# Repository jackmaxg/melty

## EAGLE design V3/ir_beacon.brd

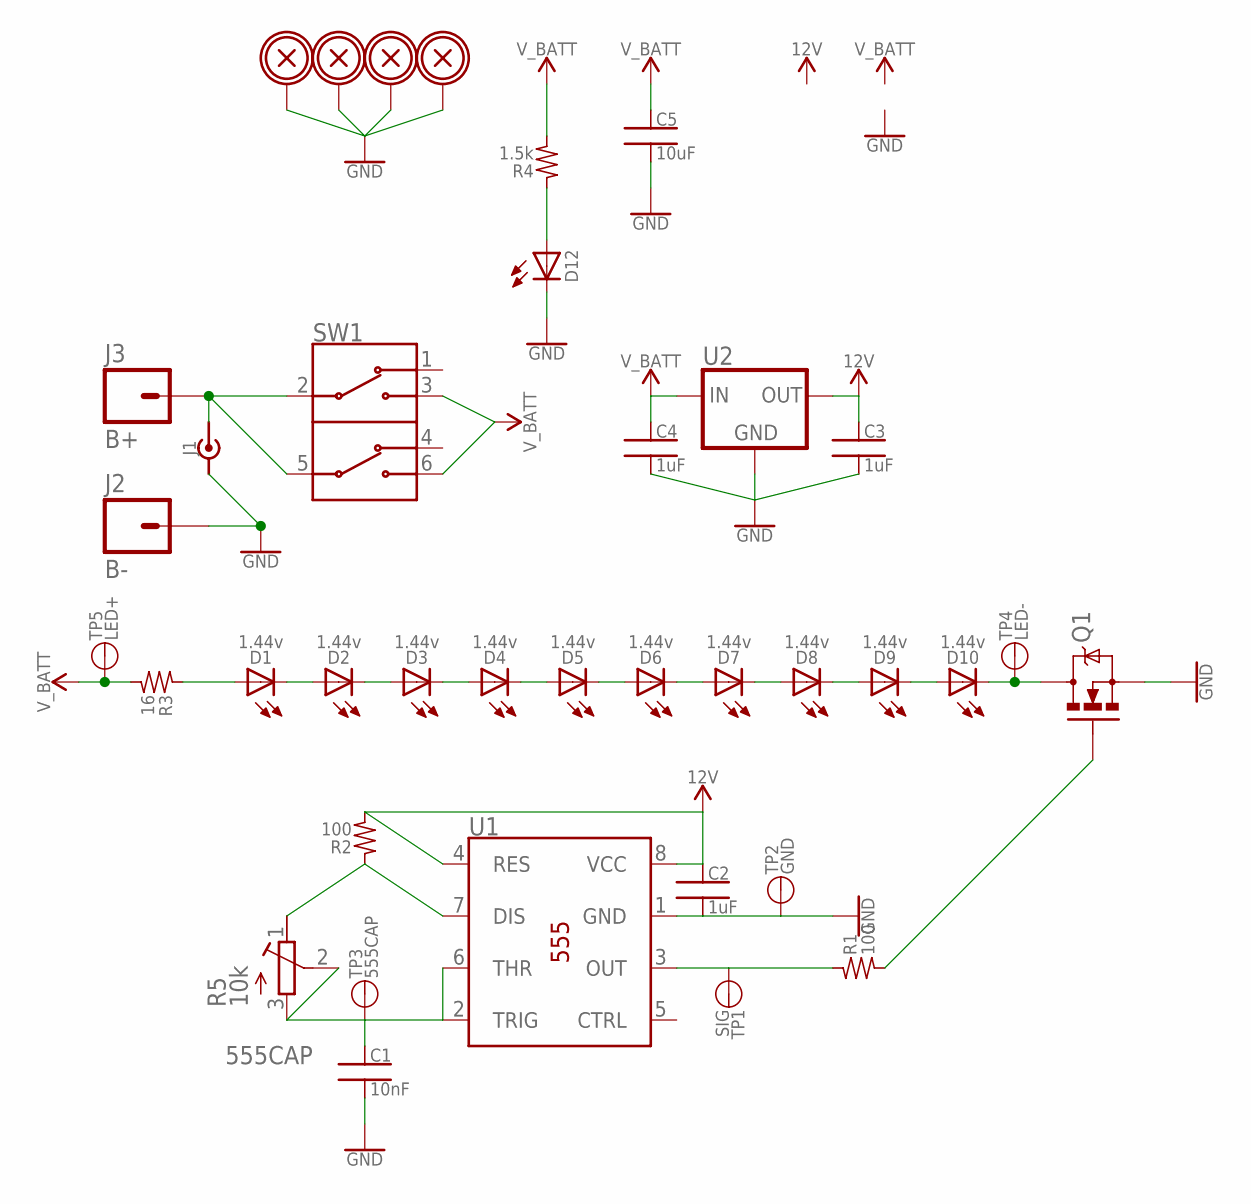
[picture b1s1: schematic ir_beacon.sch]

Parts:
C1: 10nF; CAP-PTH-.1"
C2, C3, C4: 1uF; 0805
C5: 10uF; 0805
D1, D2, D3, D4, D5, D6, D7, D8, D9, D10: 1.44v; PLCC-2
D12: LED1206; LED-1206
H1, H2, H3, H4: BOLTHOLE_M3; M3_HOLE
J1: PJ-082BH
J2: B-; 14AWG_PTH
J3: B+; 14AWG_PTH
Q1: MOSFET_N-CHANNEL_DPAK; DPAK
R1, R2: 100; 0805
R3: 16; 1206
R4: 1.5k; 0805
R5: 10k; 3296W
SW1: CNK-L202_MS02; CNK-L202XXXMS02XXX
TP1: SIG; 1X01
TP2: GND; 1X01
TP3: 555CAP; 1X01
TP4: LED-; 1X01
TP5: LED+; 1X01
U1: 555_TIMER_DIP8; DIL08
U2: 78XX_VREG_DPAK; DPAK

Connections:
12V: C2.1, C3.1, R2.2, U1.4 (RES), U1.8 (VCC), U2.3 (OUT)
555CAP: C1.1, R5.2 (S), R5.3 (A), TP3.1, U1.2 (TRIG), U1.6 (THR)
B+: J1.1, J3.P, SW1.2 (I1), SW1.5 (I2)
GND: C1.2, C2.2, C3.2, C4.2, C5.2, D12.C, H1.P, H2.P, H3.P, H4.P, J1.2, J1.SH1 (2), J1.SH2 (2), J1.SH3 (2), J1.SH4 (2), J2.P, Q1.3 (S), TP2.1, U1.1 (GND), U2.4 (GND)
unnamed: D1.A, R3.1
unnamed: D1.C, D2.A
unnamed: D2.C, D3.A
unnamed: D3.C, D4.A
unnamed: D4.C, D5.A
unnamed: D5.C, D6.A
unnamed: D6.C, D7.A
unnamed: D7.C, D8.A
unnamed: D8.C, D9.A
unnamed: D9.C, D10.A
unnamed: D10.C, Q1.4 (D), TP4.1
unnamed: D12.A, R4.1
unnamed: R1.1, TP1.1, U1.3 (OUT)
unnamed: Q1.1 (G), R1.2
unnamed: R2.1, R5.1 (E), U1.7 (DIS)
V_BATT: C4.1, C5.1, R3.2, R4.2, SW1.3 (O1B), SW1.6 (O2B), TP5.1, U2.1 (IN)

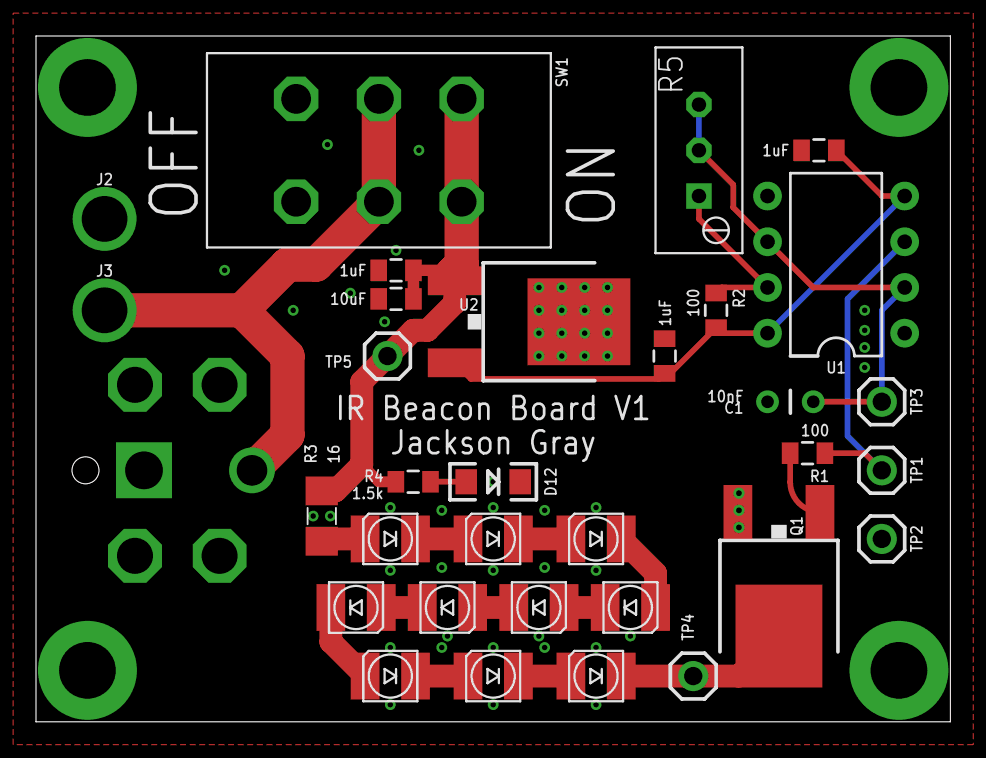
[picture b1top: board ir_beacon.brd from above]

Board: 2 copper layers, 50.8 x 38.1 mm, 37 parts (1 on the bottom side), 20 nets.

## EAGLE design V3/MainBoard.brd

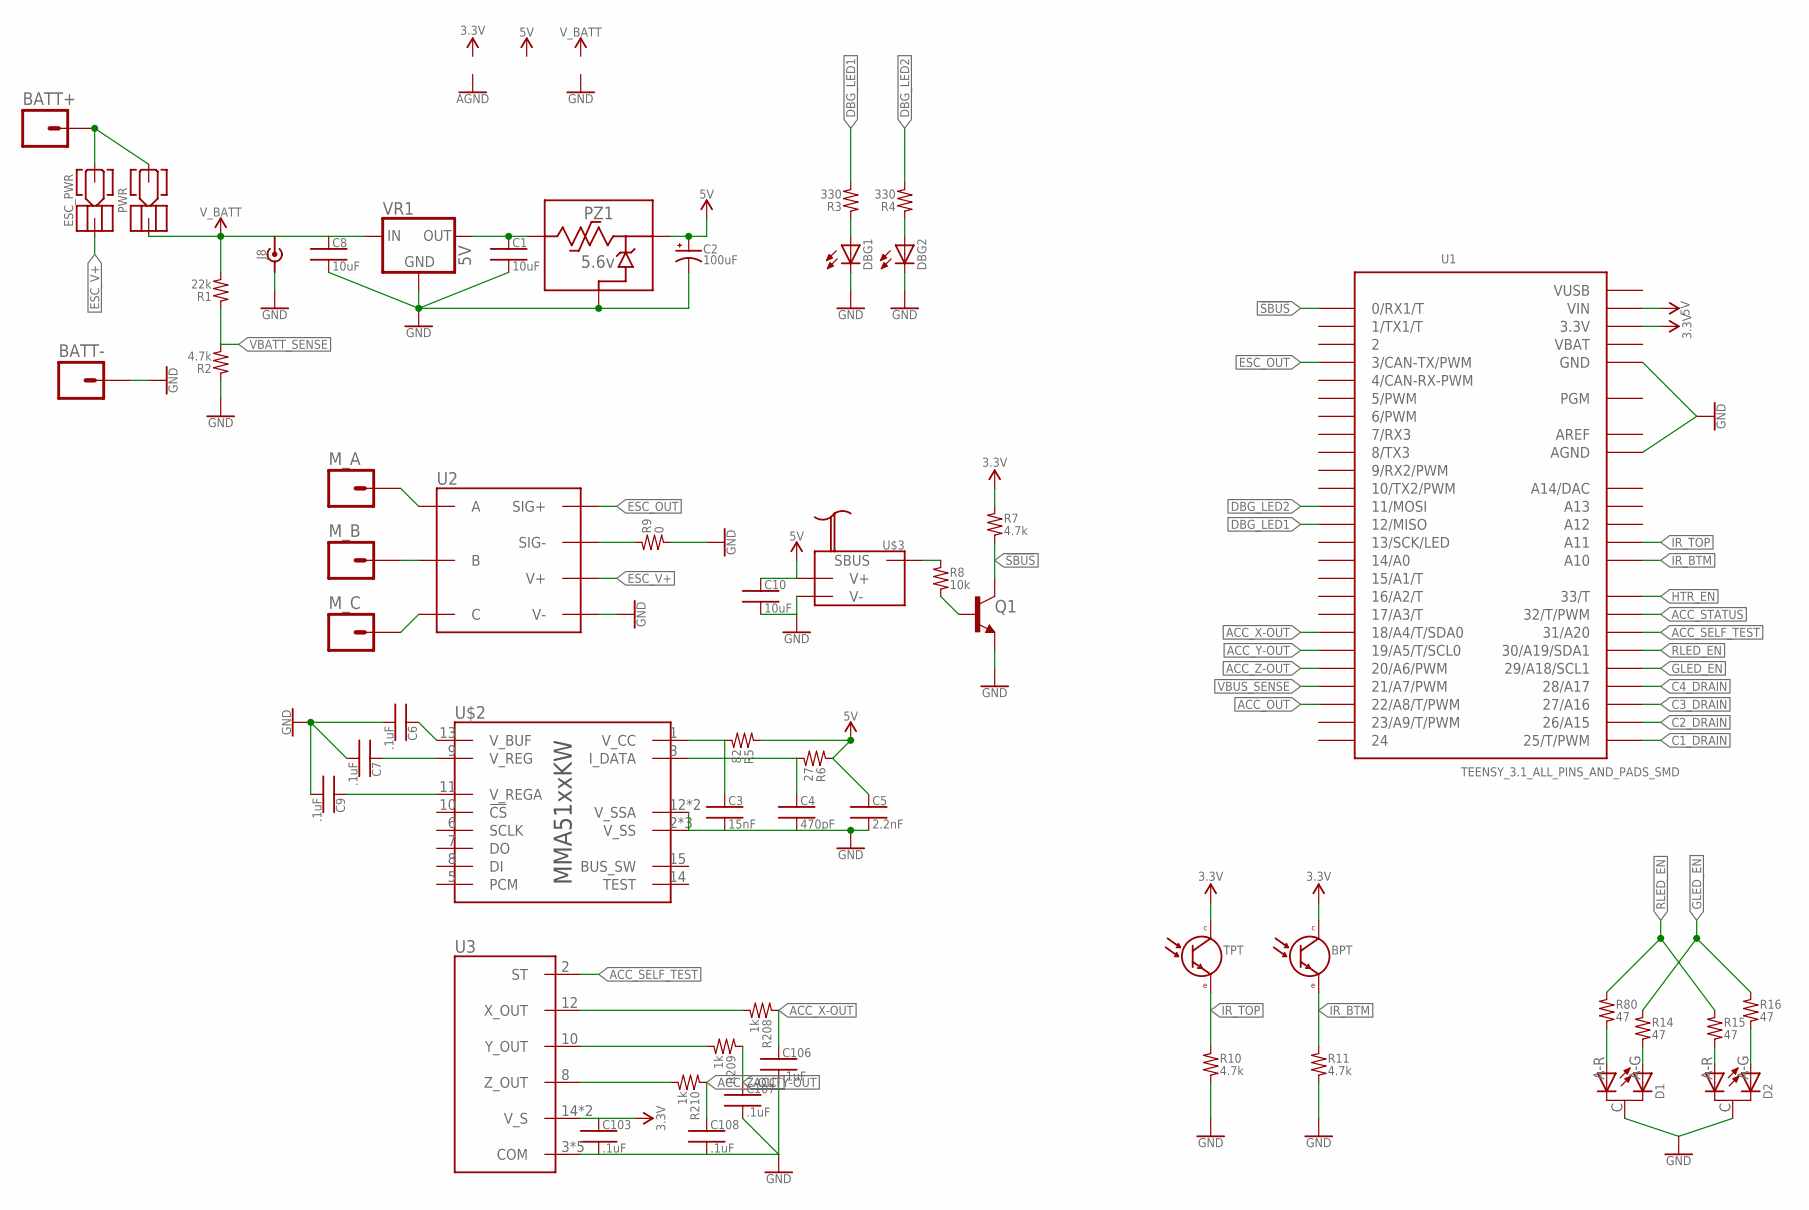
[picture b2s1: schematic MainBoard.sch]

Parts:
BATT+: 14AWG_PTH
BATT-: 14AWG_PTH
BPT: PHOTOTRANSISTOR_OPXXX-H; OP550+_HORIZ
C1, C8, C10: 10uF; 0805
C2: 100uF; 2917_D-CASE
C3: 15nF; 0805
C4: 470pF; 0805
C5: 2.2nF; 0805
C6, C7, C9, C103, C106, C107, C108: .1uF; 0805
D1, D2: TLVS5100; TLSV5100
DBG1, DBG2: LED1206; LED-1206
ESC_PWR: SCREW_SW_M3
J8: PJ-082BH
M_A: 14AWG_PTH
M_B: 14AWG_PTH
M_C: 14AWG_PTH
PWR: SCREW_SW_M3
PZ1: 5.6v; POLYZEN_LS
Q1: BJT_NPN; SOT23-3
R1: 22k; 0805
R2, R7, R10, R11: 4.7k; 0805
R3, R4: 330; 0805
R5: 82; 0805
R6: 27; 0805
R8: 10k; 0805
R9: 0; 0805
R14, R15, R16, R80: 47; 0805
R208, R209, R210: 1k; 0805
TPT: PHOTOTRANSISTOR_OPXXX-H; OP550+_HORIZ
U1: TEENSY_3.1_ALL_PINS_AND_PADS_SMD; TEENSY_3.1_SMD_ALLPINS
U2: ZTW_30A_BLDCESC; ZTW_SPIDER_30A_HV_OPTO_ESC
U3: ADXL326_QFN16; QFN16
U$2: MMA51XXKW; QFN16
U$3: SBUS_RC_RX_FRSKY-XMPM; FRSKY_XM_PLUS_MINI
VR1: 5V; TSR_2-XXXX

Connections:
3.3V: BPT.C, C103.1, R7.1, TPT.C, U1.3.3V, U1.3.3V1 (3.3V), U1.3.3V2 (3.3V), U3.14 (V_S), U3.15 (V_S)
5V: C2.A+ (+), C5.1, C10.1, PZ1.VOUT (V_OUT), R5.1, R6.1, U1.VIN, U$3.5V (V+)
!SBUS: Q1.3 (C), R7.2, U1.0 (0/RX1/T)
ACC_OUT: U1.22/A8 (22/A8/T/PWM)
ACC_SELF_TEST: U1.31 (31/A20), U3.2 (ST)
ACC_STATUS: U1.32 (32/T/PWM)
ACC_X-OUT: C106.1, R208.1, U1.18/A4 (18/A4/T/SDA0)
ACC_Y-OUT: C107.1, R209.1, U1.19/A5 (19/A5/T/SCL0)
ACC_Z-OUT: C108.1, R210.1, U1.20/A6 (20/A6/PWM)
AREF: U1.AREF
C1_DRAIN: U1.25 (25/T/PWM)
C2_DRAIN: U1.26 (26/A15)
C3_DRAIN: U1.27 (27/A16)
C4_DRAIN: U1.28 (28/A17)
DBG_LED1: R3.2, U1.12 (12/MISO)
DBG_LED2: R4.2, U1.11 (11/MOSI)
ESC_OUT: U1.3 (3/CAN-TX/PWM), U2.S+ (SIG+)
ESC_V+: ESC_PWR.BLK, U2.V0+ (V+), U2.V1+ (V+), U2.V2+ (V+), U2.V3+ (V+), U2.V4+ (V+)
GLED_EN: R14.1, R16.1, U1.29 (29/A18/SCL1)
GND: BATT-.P, C1.2, C2.C- (-), C3.2, C4.2, C5.2, C6.2, C7.2, C8.2, C9.2, C10.2, C103.2, C106.2, C107.2, C108.2, D1.C, D2.C, DBG1.C, DBG2.C, J8.2, J8.SH1 (2), J8.SH2 (2), J8.SH3 (2), J8.SH4 (2), PZ1.GND, Q1.2 (E), R2.1, R9.2, R10.2, R11.2, U1.AGND, U1.GND, U1.GND1 (GND), U1.GND2 (GND), U2.V0- (V-), U2.V1- (V-), U2.V2- (V-), U2.V3- (V-), U2.V4- (V-), U3.3 (COM), U3.5 (COM), U3.6 (COM), U3.7 (COM), U3.17 (COM), U$2.2 (V_SS), U$2.4 (V_SS), U$2.12 (V_SSA), U$2.16 (V_SSA), U$2.17 (V_SS), U$3.GND (V-), VR1.2 (GND)
HTR_EN: U1.33 (33/T)
IR_BTM: BPT.E, R11.1, U1.A10
IR_TOP: R10.1, TPT.E, U1.A11
unnamed: M_A.P, U2.A0 (A), U2.A1 (A), U2.A2 (A), U2.A3 (A), U2.A4 (A)
unnamed: M_B.P, U2.B0 (B), U2.B1 (B), U2.B2 (B), U2.B3 (B), U2.B4 (B)
unnamed: M_C.P, U2.C0 (C), U2.C1 (C), U2.C2 (C), U2.C3 (C), U2.C4 (C)
unnamed: C9.1, U$2.11 (V_REGA)
unnamed: C7.1, U$2.9 (V_REG)
unnamed: C6.1, U$2.13 (V_BUF)
unnamed: R8.1, U$3.SBUS
unnamed: C3.1, R5.2, U$2.1 (V_CC)
unnamed: C4.1, R6.2, U$2.3 (I_DATA)
unnamed: R9.1, U2.S- (SIG-)
unnamed: Q1.1 (B), R8.2
unnamed: BATT+.P, ESC_PWR.BLT, PWR.BLT
unnamed: D1.A-R (A1), R80.2
unnamed: D1.A-G (A2), R14.2
unnamed: D2.A-R (A1), R15.2
unnamed: D2.A-G (A2), R16.2
unnamed: R208.2, U3.12 (X_OUT)
unnamed: R209.2, U3.10 (Y_OUT)
unnamed: R210.2, U3.8 (Z_OUT)
unnamed: DBG2.A, R4.1
unnamed: DBG1.A, R3.1
unnamed: C1.1, PZ1.VIN (V_IN), VR1.3 (OUT)
RLED_EN: R15.1, R80.1, U1.30 (30/A19/SDA1)
VBAT: U1.VBAT
VBATT_SENSE: R1.1, R2.2
VBUS_SENSE: U1.21/A7 (21/A7/PWM)
VUSB: U1.VUSB
V_BATT: C8.1, J8.1, PWR.BLK, R1.2, VR1.1 (IN)

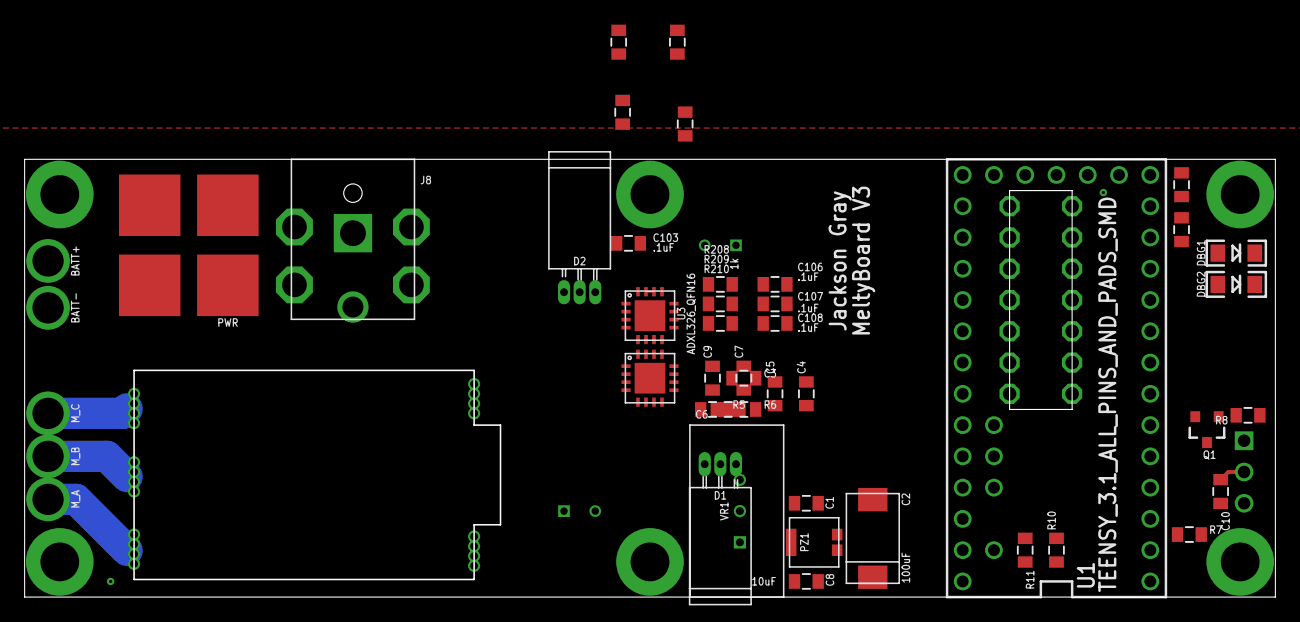
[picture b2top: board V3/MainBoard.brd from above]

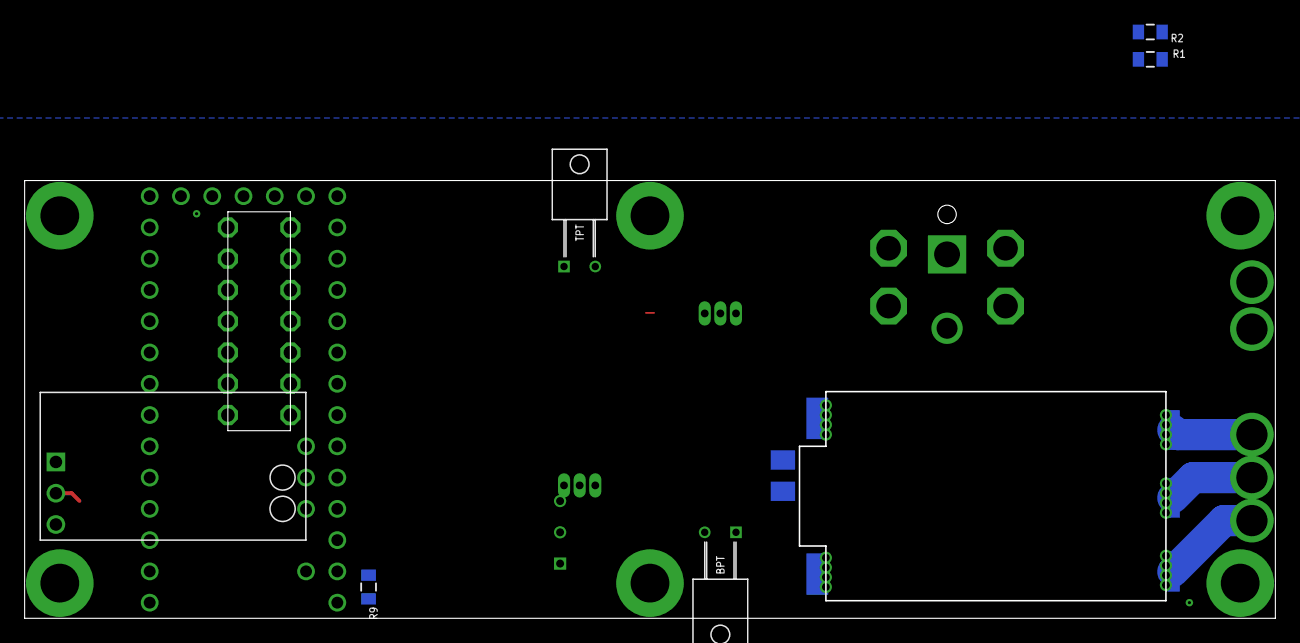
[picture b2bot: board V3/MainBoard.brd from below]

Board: 2 copper layers, 101.6 x 35.6 mm, 54 parts (7 on the bottom side), 40 nets.

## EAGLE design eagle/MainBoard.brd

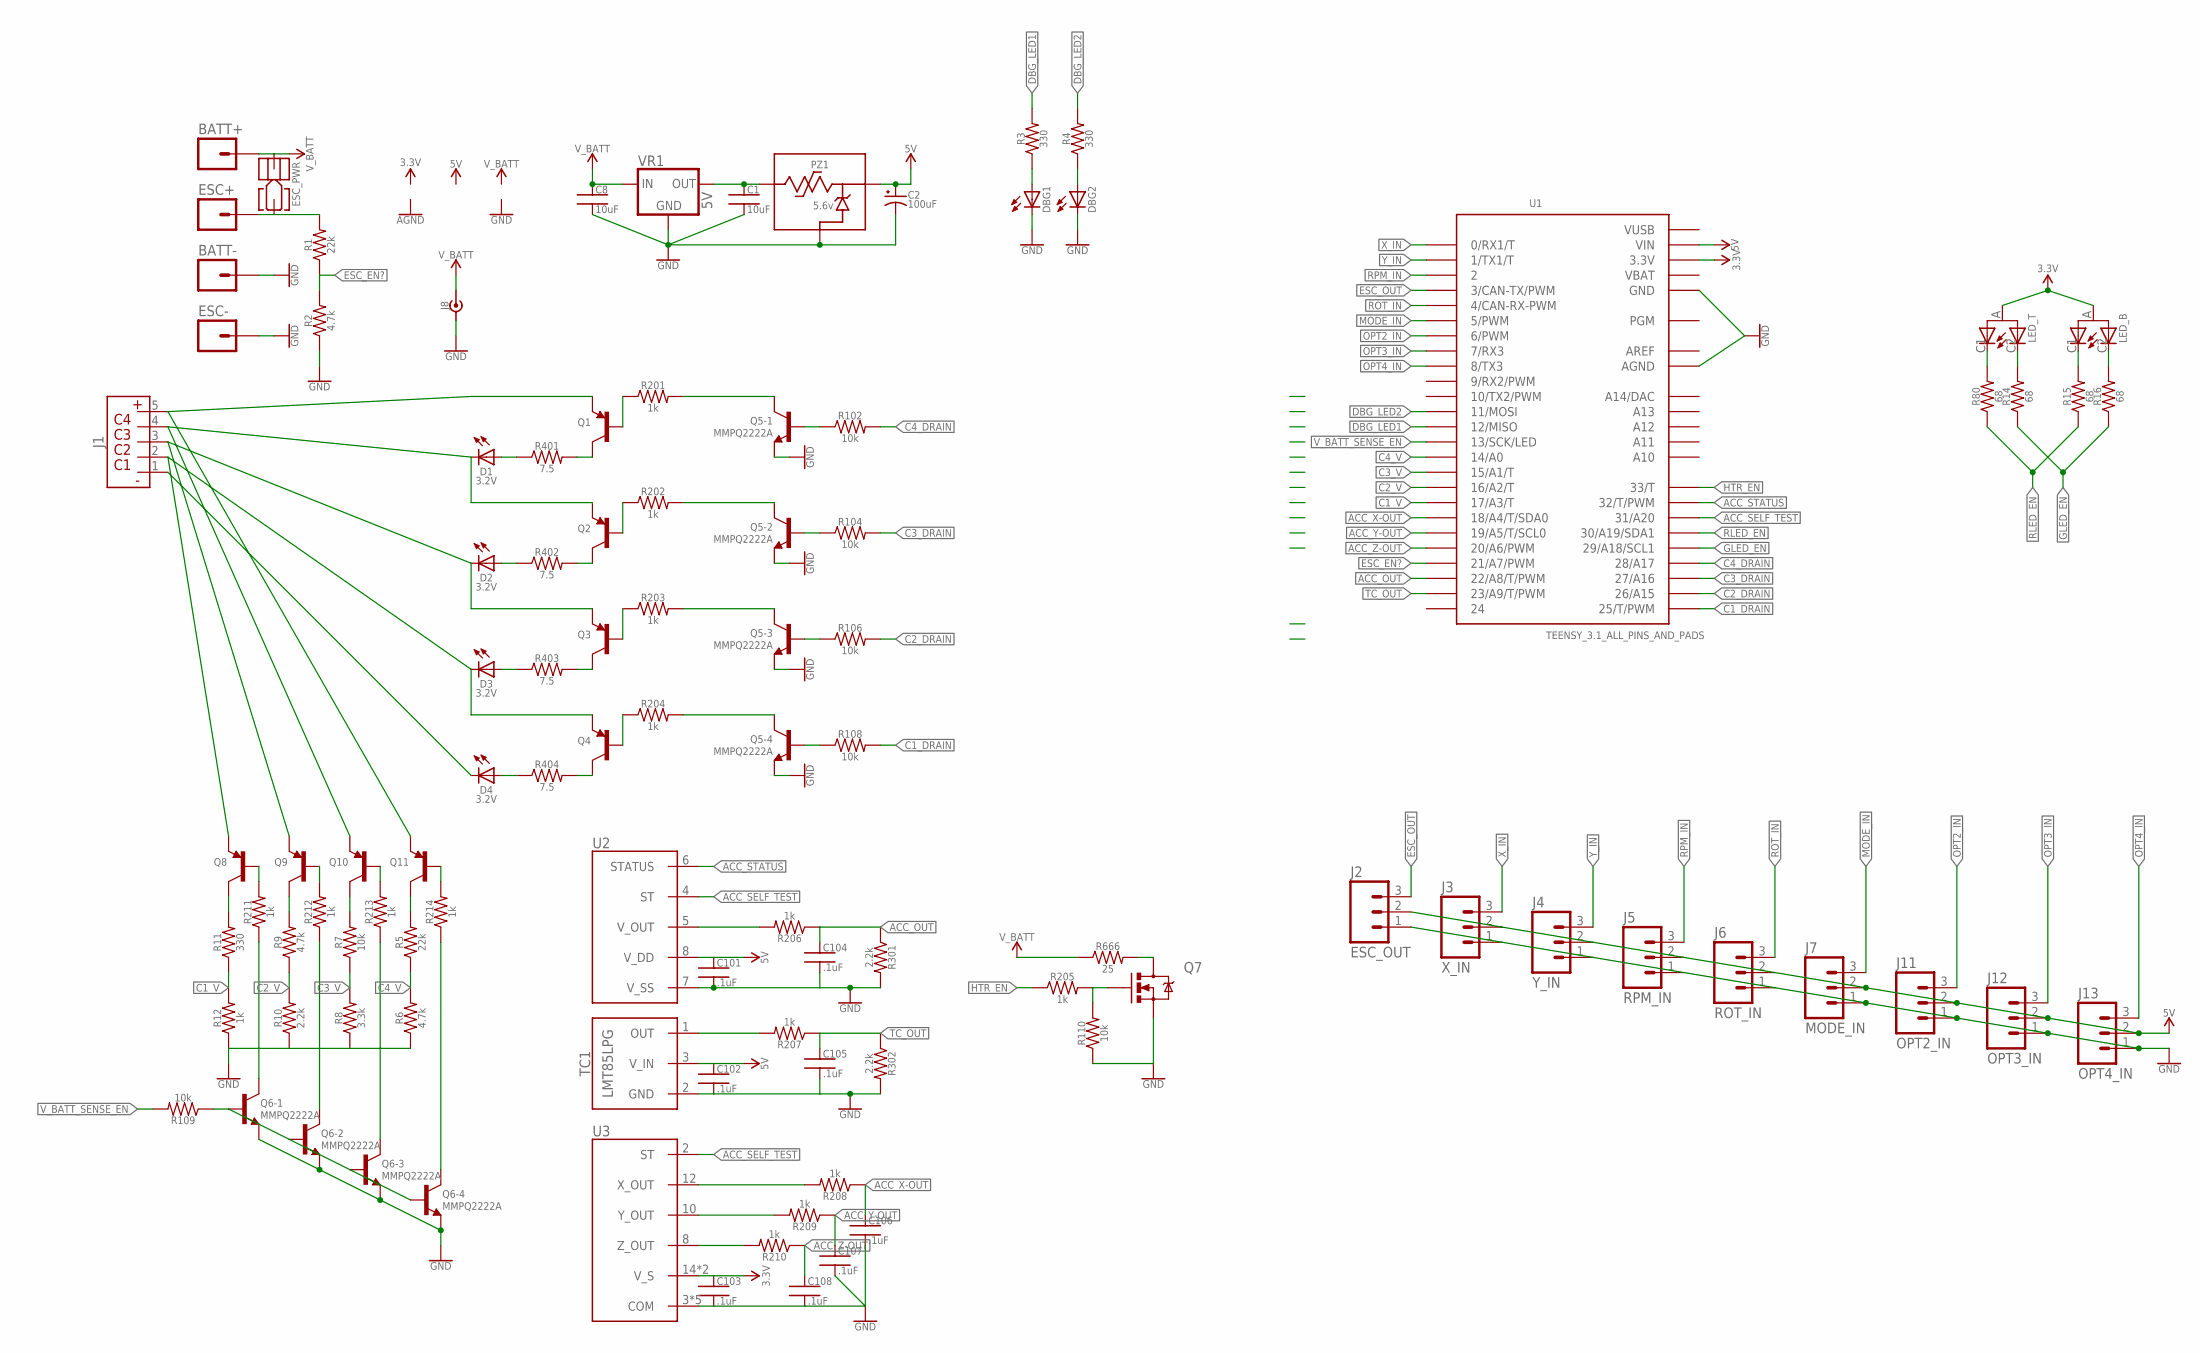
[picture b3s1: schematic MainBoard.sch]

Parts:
BATT+: 14AWG; 14AWG_SMD
BATT-: 14AWG; 14AWG_SMD
C1, C8: 10uF; 0805
C2: 100uF; 2917_D-CASE
C101, C102, C103, C104, C105, C106, C107, C108: .1uF; 0805
D1, D2, D3, D4: 3.2V; LED-2835
DBG1, DBG2: LED1206; LED-1206
ESC+: 14AWG; 14AWG_SMD
ESC-: 14AWG; 14AWG_SMD
ESC_PWR: JACK_PWR_SCREW
J1: BATT_BALANCER_PLUG_4S; JST_MALE_5_PIN
J2: ESC_OUT; 1X03
J3: X_IN; 1X03
J4: Y_IN; 1X03
J5: RPM_IN; 1X03
J6: ROT_IN; 1X03
J7: MODE_IN; 1X03
J8: PJ-082BH
J11: OPT2_IN; 1X03
J12: OPT3_IN; 1X03
J13: OPT4_IN; 1X03
LED_B: DIALIGHT_597-2751-607F; DIALIGHT_1208_BI-COLOR
LED_T: DIALIGHT_597-2751-607F; DIALIGHT_1208_BI-COLOR
PZ1: 5.6v; POLYZEN_LS
Q1, Q2, Q3, Q4, Q8, Q9, Q10, Q11: BJT_PNP; SOT23-3
Q5, Q6: MMPQ2222A; SOIC_16
Q7: MOSFET_N-CHANNEL_SOT23-3; SOT23-3
R1, R5: 22k; 0805
R2, R6, R9: 4.7k; 0805
R3, R4, R11: 330; 0805
R7, R102, R104, R106, R108, R109, R110: 10k; 0805
R8: 3.3k; 0805
R10, R301, R302: 2.2k; 0805
R12, R201, R202, R203, R204, R205, R206, R207, R208, R209, R210, R211, R212, R213, R214: 1k; 0805
R14, R15, R16, R80: 68; 0805
R401, R402, R403, R404: 7.5; 1206
R666: 25; TO-220-R
TC1: LMT85LPG; TO-92
U1: TEENSY_3.1_ALL_PINS_AND_PADS; TEENSY_3.1_ALLPINS
U2: MMA1211KEG; SOIC_16_WIDE
U3: ADXL326; LFCSP_LQ
VR1: 5V; TSR_2-XXXX

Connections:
3.3V: C103.1, LED_B.A, LED_T.A, U1.3.3V, U1.3.3V1 (3.3V), U1.3.3V2 (3.3V), U3.14 (V_S), U3.15 (V_S)
5V: C2.A+ (+), C101.1, C102.1, J2.2, J3.2, J4.2, J5.2, J6.2, J7.2, J11.2, J12.2, J13.2, PZ1.VOUT (V_OUT), TC1.3 (V_IN), U1.VIN, U2.8 (V_DD)
ACC_OUT: C104.1, R206.1, R301.1, U1.22/A8 (22/A8/T/PWM)
ACC_SELF_TEST: U1.31 (31/A20), U2.4 (ST), U3.2 (ST)
ACC_STATUS: U1.32 (32/T/PWM), U2.6 (STATUS)
ACC_X-OUT: C106.1, R208.1, U1.18/A4 (18/A4/T/SDA0)
ACC_Y-OUT: C107.1, R209.1, U1.19/A5 (19/A5/T/SCL0)
ACC_Z-OUT: C108.1, R210.1, U1.20/A6 (20/A6/PWM)
AREF: U1.AREF
C1_DRAIN: R108.2, U1.25 (25/T/PWM)
C1_V: R11.1, R12.2, U1.17/A3 (17/A3/T)
C2_DRAIN: R106.2, U1.26 (26/A15)
C2_V: R9.1, R10.2, U1.16/A2 (16/A2/T)
C3_DRAIN: R104.2, U1.27 (27/A16)
C3_V: R7.1, R8.2, U1.15/A1 (15/A1/T)
C4_DRAIN: R102.2, U1.28 (28/A17)
C4_V: R5.1, R6.2, U1.14/A0
DBG_LED1: R3.2, U1.12 (12/MISO)
DBG_LED2: R4.2, U1.11 (11/MOSI)
ESC+: ESC+.P, ESC_PWR.1, R1.2
ESC_EN?: R1.1, R2.2, U1.21/A7 (21/A7/PWM)
ESC_OUT: J2.3, U1.3 (3/CAN-TX/PWM)
GLED_EN: R14.1, R16.1, U1.29 (29/A18/SCL1)
GND: BATT-.P, C1.2, C2.C- (-), C8.2, C101.2, C102.2, C103.2, C104.2, C105.2, C106.2, C107.2, C108.2, DBG1.C, DBG2.C, ESC-.P, J2.1, J3.1, J4.1, J5.1, J6.1, J7.1, J8.2, J8.SH1 (2), J8.SH2 (2), J8.SH3 (2), J8.SH4 (2), J11.1, J12.1, J13.1, PZ1.GND, Q5.10 (E), Q5.12 (E), Q5.14 (E), Q5.16 (E), Q6.10 (E), Q6.12 (E), Q6.14 (E), Q6.16 (E), Q7.2 (S), R2.1, R6.1, R8.1, R10.1, R12.1, R110.1, R301.2, R302.2, TC1.2 (GND), U1.AGND, U1.GND, U1.GND1 (GND), U1.GND2 (GND), U2.7 (V_SS), U3.3 (COM), U3.5 (COM), U3.6 (COM), U3.7 (COM), U3.17 (COM), VR1.2 (GND)
HTR_EN: R205.1, U1.33 (33/T)
MODE_IN: J7.3, U1.5 (5/PWM)
unnamed: D1.A, R401.1
unnamed: Q1.3 (C), R401.2
unnamed: Q1.1 (B), R201.1
unnamed: Q5.1 (C), Q5.2 (C), R201.2
unnamed: J1.5 (C4), Q1.2 (E), Q11.2 (E)
unnamed: Q5.15 (B), R102.1
unnamed: Q7.3 (D), R666.2
unnamed: D2.A, R402.1
unnamed: Q2.3 (C), R402.2
unnamed: Q2.1 (B), R202.1
unnamed: Q5.3 (C), Q5.4 (C), R202.2
unnamed: D1.C, J1.4 (C3), Q2.2 (E), Q10.2 (E)
unnamed: Q5.13 (B), R104.1
unnamed: D3.A, R403.1
unnamed: Q3.3 (C), R403.2
unnamed: Q3.1 (B), R203.1
unnamed: Q5.5 (C), Q5.6 (C), R203.2
unnamed: D2.C, J1.3 (C2), Q3.2 (E), Q9.2 (E)
unnamed: Q5.11 (B), R106.1
unnamed: D4.A, R404.1
unnamed: Q4.3 (C), R404.2
unnamed: Q4.1 (B), R204.1
unnamed: Q5.7 (C), Q5.8 (C), R204.2
unnamed: D3.C, J1.2 (C1), Q4.2 (E), Q8.2 (E)
unnamed: Q5.9 (B), R108.1
unnamed: D4.C, J1.1 (V0)
unnamed: Q7.1 (G), R110.2, R205.2
unnamed: R206.2, U2.5 (V_OUT)
unnamed: Q8.3 (C), R11.2
unnamed: Q8.1 (B), R211.2
unnamed: Q6.1 (C), Q6.2 (C), R211.1
unnamed: Q9.1 (B), R212.2
unnamed: Q6.9 (B), Q6.11 (B), Q6.13 (B), Q6.15 (B), R109.1
unnamed: R208.2, U3.12 (X_OUT)
unnamed: R209.2, U3.10 (Y_OUT)
unnamed: R210.2, U3.8 (Z_OUT)
unnamed: R207.2, TC1.1 (OUT)
unnamed: Q6.3 (C), Q6.4 (C), R212.1
unnamed: Q10.3 (C), R7.2
unnamed: Q10.1 (B), R213.2
unnamed: Q6.5 (C), Q6.6 (C), R213.1
unnamed: Q11.3 (C), R5.2
unnamed: Q11.1 (B), R214.2
unnamed: Q6.7 (C), Q6.8 (C), R214.1
unnamed: Q9.3 (C), R9.2
unnamed: DBG2.A, R4.1
unnamed: DBG1.A, R3.1
unnamed: C1.1, PZ1.VIN (V_IN), VR1.3 (OUT)
unnamed: LED_T.C1, R80.2
unnamed: LED_T.C2, R14.2
unnamed: LED_B.C1, R15.2
unnamed: LED_B.C2, R16.2
OPT2_IN: J11.3, U1.6 (6/PWM)
OPT3_IN: J12.3, U1.7 (7/RX3)
OPT4_IN: J13.3, U1.8 (8/TX3)
RLED_EN: R15.1, R80.1, U1.30 (30/A19/SDA1)
ROT_IN: J6.3, U1.4 (4/CAN-RX-PWM)
RPM_IN: J5.3, U1.2
TC_OUT: C105.1, R207.1, R302.1, U1.23/A9 (23/A9/T/PWM)
VBAT: U1.VBAT
VUSB: U1.VUSB
V_BATT: BATT+.P, C8.1, ESC_PWR.2, J8.1, R666.1, VR1.1 (IN)
V_BATT_SENSE_EN: R109.2, U1.13 (13/SCK/LED)
X_IN: J3.3, U1.0 (0/RX1/T)
Y_IN: J4.3, U1.1 (1/TX1/T)

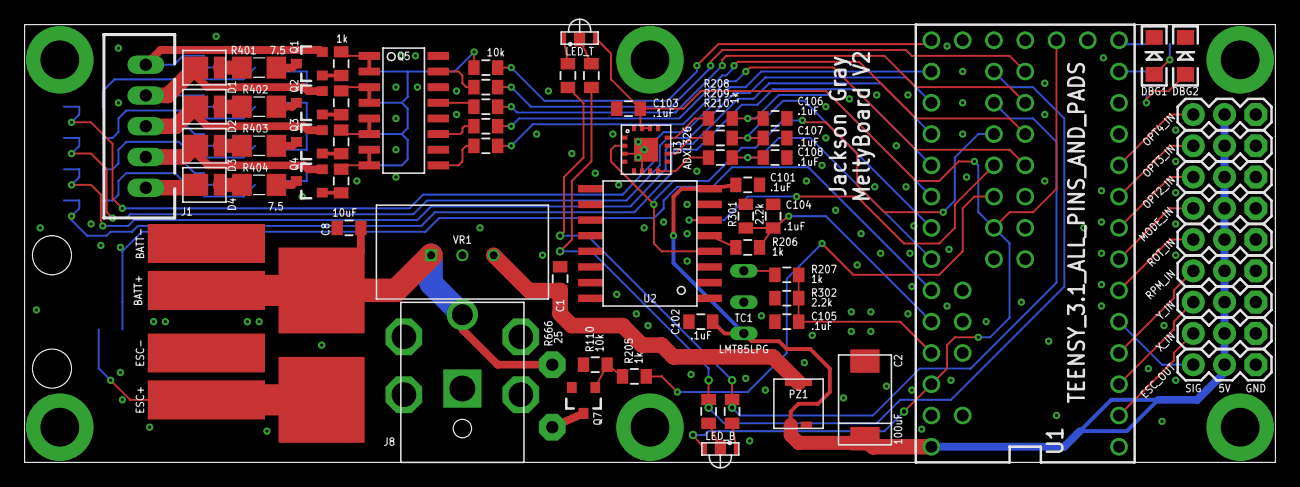
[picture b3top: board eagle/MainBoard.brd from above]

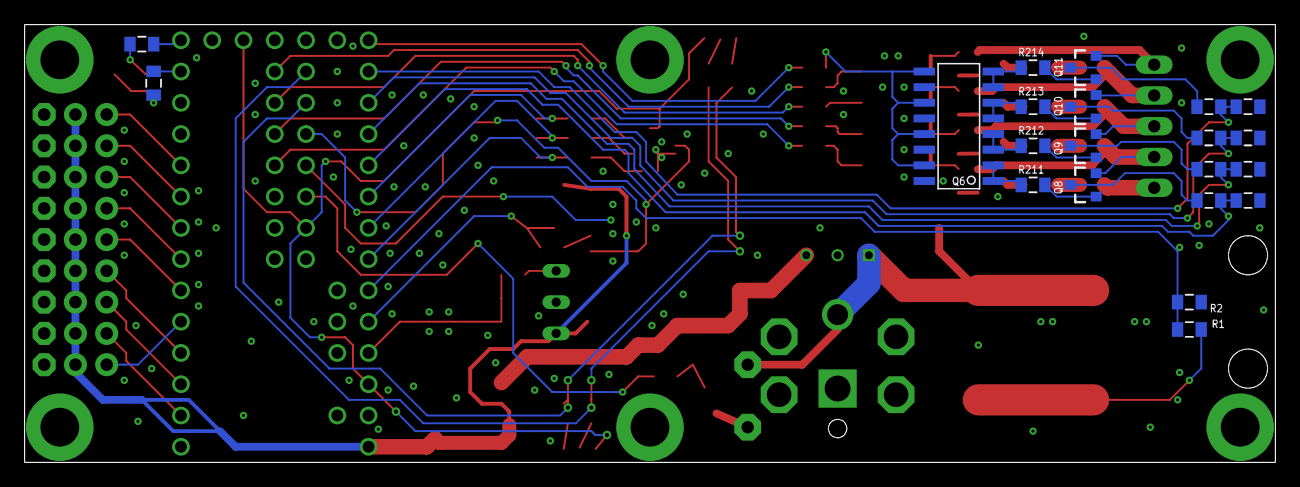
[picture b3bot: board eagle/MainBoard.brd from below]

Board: 2 copper layers, 101.6 x 35.6 mm, 95 parts (21 on the bottom side), 88 nets.

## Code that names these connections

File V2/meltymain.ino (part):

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#define ONESHOT_MAX_HZ 3000

//pinouts
#define X_IN 0
#define Y_IN 1
#define RPM_IN 2
#define ESC_OUT 3
#define ROT_IN 4
#define MODE_IN 5 //was formerly OPT1, which is why we start at OPT2
#define OPT2_IN 6 //will be used for trim
#define OPT3_IN 7
#define OPT4_IN 8
//9 no connection
//10 nc
#define DBG_LED2 11
#define DBG_LED1 12
#define V_BATT_SENSE_EN 13
#define C4_V 14
#define C3_V 15
#define C2_V 16
#define C1_V 17
#define ACC_X_OUT 18
#define ACC_Y_OUT 19
#define ACC_Z_OUT 20
#define ESC_EN 21 //actually an analog input, not output
#define ACC_OUT 22
#define TC_OUT 23
//24 nc
#define C1_DRAIN 25
#define C2_DRAIN 26
#define C3_DRAIN 27
#define C4_DRAIN 28
#define GLED_EN 29
#define RLED_EN 30
#define ACC_SELF_TEST 31
#define ACC_STATUS 32
#define HTR_EN 33

double pi_d = 3.1415926535897932384626433832795;
float pi = pi_d;
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const uint16_t orient_RSU_thresh = 502;
const uint16_t orient_USD_thresh = 522; 

const uint8_t rc_in_pins[] = {X_IN, Y_IN, RPM_IN, ROT_IN, MODE_IN, OPT2_IN, OPT3_IN, OPT4_IN};
volatile uint32_t pEdge[RC_PWM_INPUTS]; //front pulse edge
volatile boolean pHigh[RC_PWM_INPUTS];
volatile uint16_t pWidth[RC_PWM_INPUTS]; //width of pulse
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//3.965, 7.94, 11.93, 15.99
float vbus_v_ratio = 1;
float cell_v_ratio[4] = {1.4824,3.1385,4.055,7.91}; //multiply the analog reading by this to get the end voltage, set this to the resistor divider factor, will convert this to 0-1023 in setup
uint8_t cell_v_pins[4] = {C1_V, C2_V, C3_V, C4_V};
uint8_t cell_drain_pins[4] = {C1_DRAIN, C2_DRAIN, C3_DRAIN, C4_DRAIN};

void setup() {
  Serial.begin(9600);
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  t_last = 0;
  vbus = 0;

  pinMode(X_IN, INPUT);
  pinMode(Y_IN, INPUT);
  pinMode(RPM_IN, INPUT);
  pinMode(ESC_OUT, OUTPUT);
  pinMode(ROT_IN, INPUT);
  pinMode(MODE_IN, INPUT);
  pinMode(OPT2_IN, INPUT);
  pinMode(OPT3_IN, INPUT);
  pinMode(OPT4_IN, INPUT);
  //9 nc
  //10 nc
  pinMode(DBG_LED2, OUTPUT);
  pinMode(DBG_LED1, OUTPUT); 
  pinMode(V_BATT_SENSE_EN, OUTPUT);
  pinMode(C4_V, INPUT);
  pinMode(C3_V, INPUT);
  pinMode(C2_V, INPUT);
  pinMode(C1_V, INPUT);
  pinMode(ACC_X_OUT, INPUT);
  pinMode(ACC_Y_OUT, INPUT);
  pinMode(ACC_Z_OUT, INPUT);
  pinMode(ESC_EN, INPUT);
  pinMode(ACC_OUT, INPUT);
  pinMode(TC_OUT, INPUT);
  //25 nc
  pinMode(C1_DRAIN, OUTPUT);
  pinMode(C2_DRAIN, OUTPUT);
  pinMode(C3_DRAIN, OUTPUT);
  pinMode(C4_DRAIN, OUTPUT);
  pinMode(GLED_EN, OUTPUT);
  pinMode(RLED_EN, OUTPUT);
  pinMode(ACC_SELF_TEST, OUTPUT);
  pinMode(ACC_STATUS, INPUT);
  pinMode(HTR_EN, OUTPUT);

  for(uint8_t i = 0; i<4; i++) { cell_v_ratio[i] = 3.3*cell_v_ratio[i]/1024.0; voltages[i] = readBattVoltage(i); }

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    if(debug) Serial.println("No Comms");
    if(mode == 2) mode = 0;
  }
  else if(mode_in < 1250) mode = 0;
  else if(mode_in > 1750) mode = 2;
  else mode = 1;
  
  switch(mode){
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double readBattVoltage(uint8_t cellNum) { return cell_v_ratio[cellNum]*analogRead(cell_v_pins[cellNum]); }

void configOneShot125() {
  //pinMode(ESC_OUT, OUTPUT);
  digitalWrite(ESC_OUT, LOW);

  //disable write protection
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
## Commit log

2018-04-03 Initial commit of code, likely functional. Has interrupt based pulse in code for the rc inputs, but lacks oneshot125 implementation.
2018-05-05 Functional melty code as seen in first attacking of aluminum chunk. Changes primarily related to the switch from board V1 to V2, and tuning the new accelerometer
2018-05-05 First commit of the eagle files, in the state that they were when board V2 was sent out
2018-06-08 Heavily revised the project organization, mostly moved files around but most notably created a lbr for this project specifically.
2018-07-13 Changed the testpoint type slightly, added a few more to the board. Moved around some traces and added many more vias for thermal conductivity. Generated new gerbers for the beacon board.
